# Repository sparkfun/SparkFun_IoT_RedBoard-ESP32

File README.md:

SparkFun IoT RedBoard - ESP32
========================================

[*SparkFun IoT RedBoard - ESP32 (WRL-19177)*](https://www.sparkfun.com/products/19177)

The [SparkFun IoT RedBoard](www.sparkfun.com/products/19177) is an ESP32 Development Board that includes everything but the kitchen sink! Espressif's ESP32 WROOM is a powerful WiFi and Bluetooth® MCU module that targets a wide variety of applications. At the core of this module is the ESP32-D0WDQ6 chip which is designed to be both scalable and adaptive. The IoT RedBoard can target a wide variety of applications, ranging from low-power sensor networks to the most demanding tasks, such as voice encoding, music streaming, and MP3 decoding. The IoT ReadBoard also utilizes our handy Qwiic Connect System which means no soldering or shields are required to connect it to the rest of your system!

The USB-to-serial is achieved with a USB-C connector with through hole anchoring and the ubiquitous CH340G requiring fewer driver installs. We've included 3.3V voltage translation and a [Qwiic connector](https://www.sparkfun.com/qwiic) to the edge of the board to allow for quick and seamless connection to our ever-growing line of I<sup>2</sup>C based [Qwiic products](https://www.sparkfun.com/qwiic#products). The board even includes a microSD socket if your application requires you to log and save data to a memory card.

The operating system is freeRTOS with LwIP; TLS 1.2 with hardware acceleration is built in as well. Secure (encrypted) over the air (OTA) upgrade is also supported, so that users can upgrade their products even after their release, at minimum cost and effort.

Repository Contents
-------------------

* **/Documents** - Data sheets, additional product information
* **/Hardware** - Eagle design files (.brd, .sch)

Documentation
--------------
* **[SparkFun Fritzing Part](https://github.com/sparkfun/Fritzing_Parts/blob/main/products/19177_sfe_iot_redboard_esp32_development_board.fzpz)** - Fritzing diagrams for SparkFun products.
* **[Hookup Guide](https://learn.sparkfun.com/tutorials/iot-redboard-esp32-development-board-hookup-guide)** - Basic hookup guide for the SparkFun IoT RedBoard ESP32.

License Information
-------------------

This product is _**open source**_! 

Please review the LICENSE.md file for license information. 

If you have any questions or concerns on licensing, please contact technical support on our [SparkFun forums](https://forum.sparkfun.com/viewforum.php?f=152).

Distributed as-is; no warranty is given.

- Your friends at SparkFun.

_<COLLABORATION CREDIT>_

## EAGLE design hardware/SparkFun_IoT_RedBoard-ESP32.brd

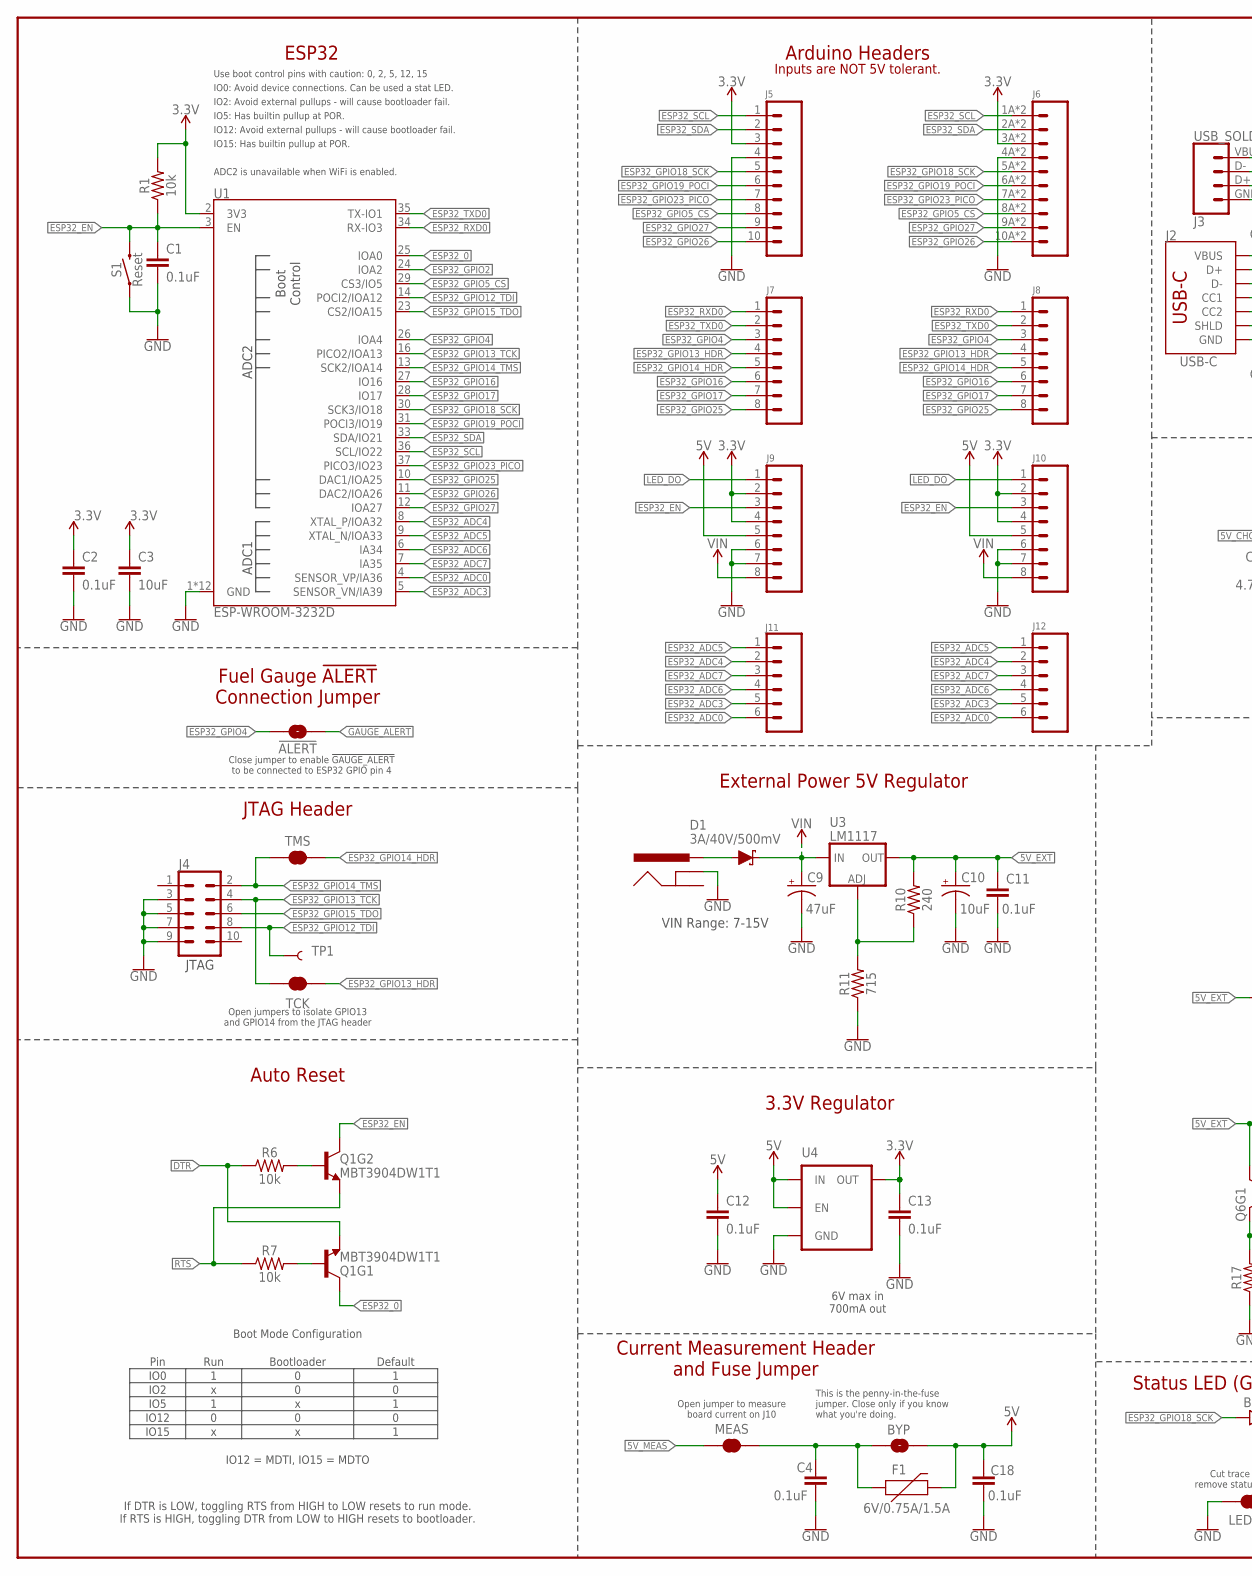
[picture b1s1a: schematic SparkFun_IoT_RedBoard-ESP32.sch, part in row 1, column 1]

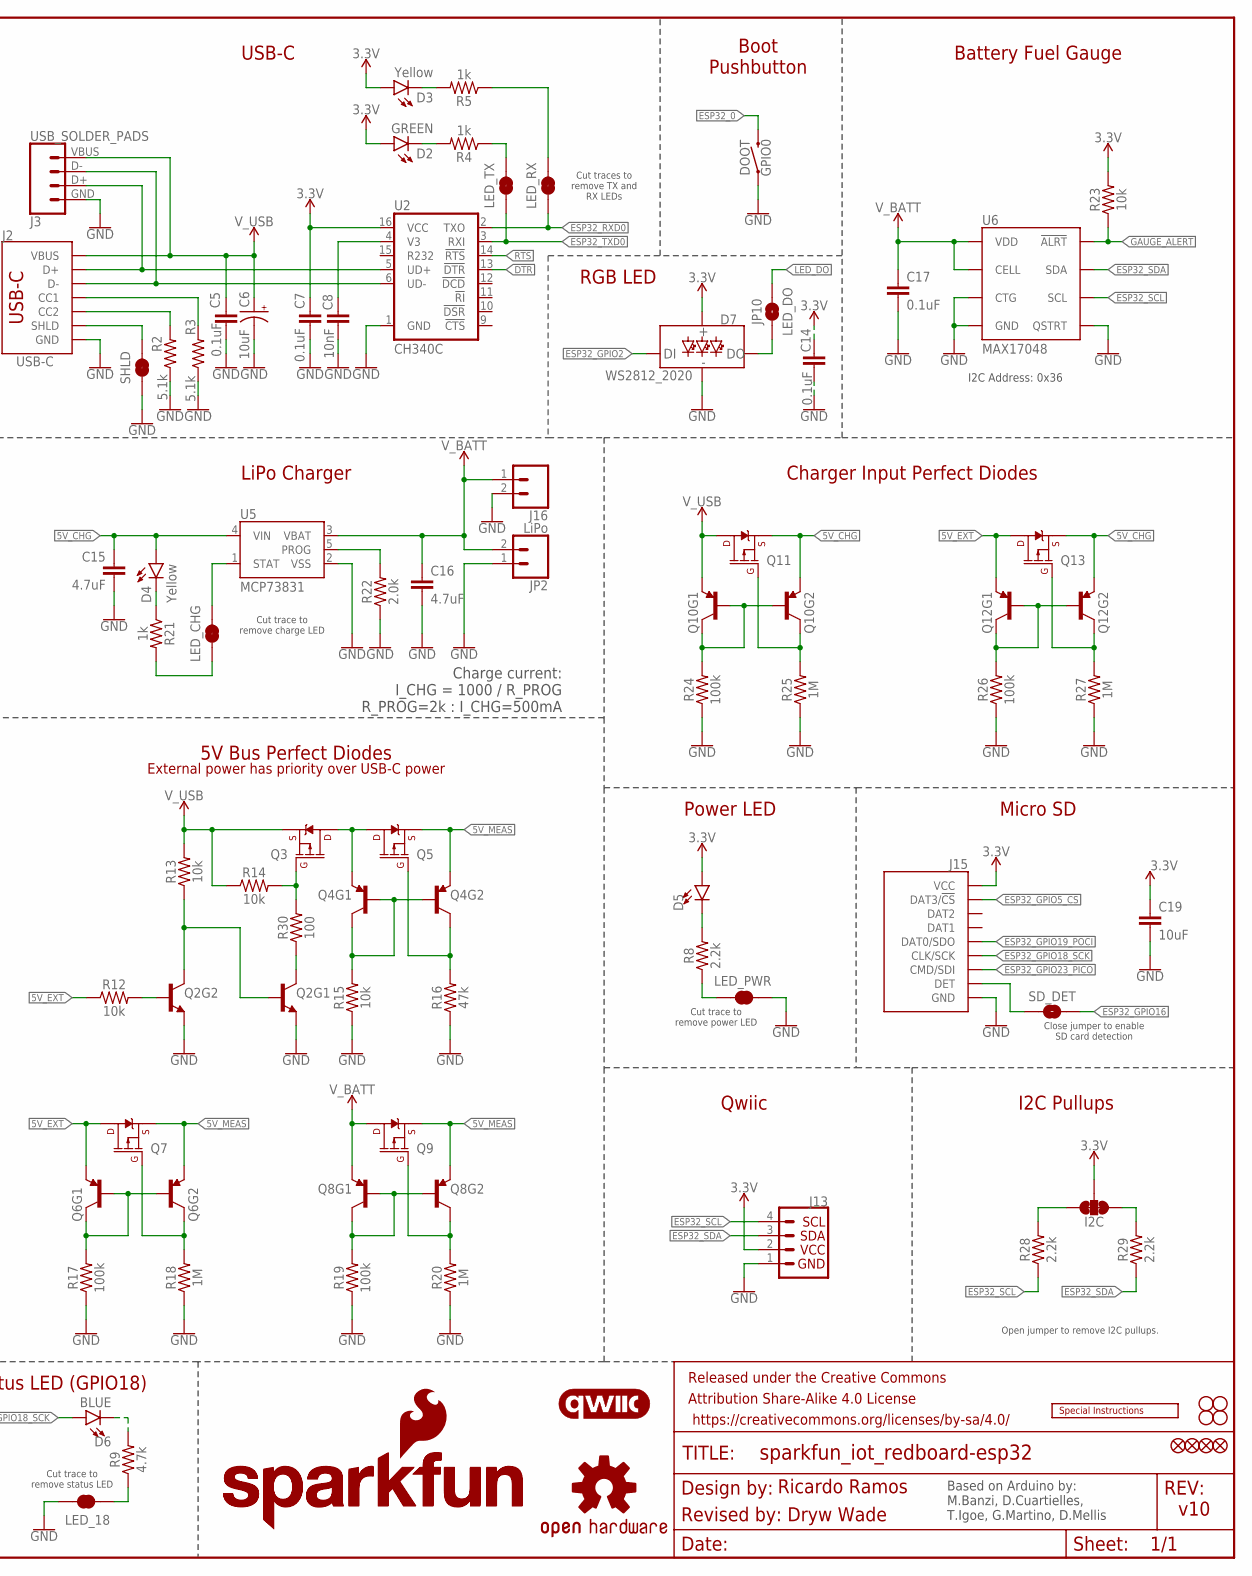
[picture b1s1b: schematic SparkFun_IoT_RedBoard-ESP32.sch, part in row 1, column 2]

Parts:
!ALERT!: JUMPER-SMT_2_NO_SILK; SMT-JUMPER_2_NO_SILK
BYP: JUMPER-SMT_2_NO_SILK; SMT-JUMPER_2_NO_SILK
C1, C2, C4, C5, C7, C11, C12, C13, C14, C17, C18: 0.1uF; 0603
C3, C19: 10uF; 0603
C6, C10: 10uF; EIA3216
C8: 10nF; 0603
C9: 47uF; PANASONIC_D
C15, C16: 4.7uF; 0603
D1: 3A/40V/500mV; SMA-DIODE
D2: GREEN; LED-1206
D3, D4: Yellow; LED-1206
D5: RED; LED-1206
D6: BLUE; LED-1206
D7: WS2812_2020; WS2812-2020
DOOT: GPIO0; TACTILE_SWITCH_SMD_5.2MM
F1: 6V/0.75A/1.5A; 1206
FRAME1: FRAME-LEDGER; CREATIVE_COMMONS
I2C: JUMPER-SMT_3_2-NC_TRACE_SILK; SMT-JUMPER_3_2-NC_TRACE_SILK
J1: 5.5x2.1mm Barrel; POWER_JACK_SMD
J2: USB-C; USB-C-16P-4LAYER-ISOLATED
J3: USB_SOLDER_PADS; USB-SOLDER-PADS
J4: CONN_05X20.05_IN_PTH_SILK; 2X5_PTH_SILK_.05
J5: M10NO_SILK; 1X10_NO_SILK
J6: CONN_10SMD_COMBO-FEMALE; 1X10_SMD_COMBINED
J7, J9: CONN_08NO_SILK_FEMALE_PTH; 1X08_NO_SILK
J8, J10: CONN_08SMD-COMBO-FEMALE; 1X08_SMD_COMBINED
J11: CONN_06NO_SILK_FEMALE_PTH; 1X06_NO_SILK
J12: CONN_06SMD-STRAIGHT-COMBO-FEMALE; 1X06_SMD_STRAIGHT_COMBO
J13: QWIIC_RIGHT_ANGLE; JST04_1MM_RA
J15: MICRO-SD-PUSH-PUSH-EXT-PIN; MICROSD-EXTERNALPIN
J16: CONN_021X02_NO_SILK; 1X02_NO_SILK
JP1, JP7, JP8, JP9: FIDUCIAL1X2; FIDUCIAL-1X2
JP2: LiPo; JST-2-SMD
JP3, JP4, JP5, JP6: STAND-OFF
JP10: LED_DO; SMT-JUMPER_2_NO_SILK
LED_18: JUMPER-SMT_2_NC_TRACE_SILK; SMT-JUMPER_2_NC_TRACE_SILK
LED_CHG: JUMPER-SMT_2_NC_TRACE_SILK; SMT-JUMPER_2_NC_TRACE_SILK
LED_PWR: JUMPER-SMT_2_NC_TRACE_SILK; SMT-JUMPER_2_NC_TRACE_SILK
LED_RX: JUMPER-SMT_2_NC_TRACE_SILK; SMT-JUMPER_2_NC_TRACE_SILK
LED_TX: JUMPER-SMT_2_NC_TRACE_SILK; SMT-JUMPER_2_NC_TRACE_SILK
LOGO1: SFE_LOGO_NAME.1_INCH; SFE_LOGO_NAME_.1
LOGO2: QWIIC_LOGO_5MM; QWIIC_5MM
LOGO3: OSHW-LOGOMINI; OSHW-LOGO-MINI
LOGO5: SPECIAL_INSTRUCTIONS-ORDERING; ORDERING_INSTRUCTIONS
LOGO6: SFE_LOGO_NAME_FLAME.2_INCH; SFE_LOGO_NAME_FLAME_.2
MEAS: JUMPER-COMBO_2_NC_TRACE; COMBO-JUMPER_2_NC_TRACE
Q1: MBT3904DW1T1; SC70-6
Q2: TRANS_NPN_DUAL-MBT3904DW1T1; SC70-6
Q3, Q5, Q7, Q9, Q11, Q13: 20V/4.2A/52mΩ/1.4W; SOT23-3
Q4, Q6, Q8, Q10, Q12: TRANS_PNP_DUALSOT-363; SOT363_PHILIPS
R1, R6, R7, R12, R13, R14, R15, R23: 10k; 0603
R2, R3: 5.1k; 0603
R4, R5, R21: 1k; 0603
R8, R28, R29: 2.2k; 0603
R9: 4.7k; 0603
R10: 240; 0603
R11: 715; 0603
R16: 47k; 0603
R17, R19, R24, R26: 100k; 0603
R18, R20, R25, R27: 1M; 0603
R22: 2.0k; 0603
R30: 100; 0603
S1: Reset; TACTILE_SWITCH_SMD_5.2MM
SD_DET: SD_DET; SMT-JUMPER_2_NO_SILK
SHLD: SHLD; SMT-JUMPER_2_NC_TRACE_SILK
TCK: JUMPER-SMT_2_NC_TRACE_SILK; SMT-JUMPER_2_NC_TRACE_SILK
TMS: JUMPER-SMT_2_NC_TRACE_SILK; SMT-JUMPER_2_NC_TRACE_SILK
TP1: TEST-POINT3; PAD.03X.03
U1: ESP-WROOM-3232D; ESP-WROOM-32D
U2: CH340C; SO016
U3: LM1117; SOT223
U4: XC6222B331MR-G; SOT23-5
U5: MCP73831; SOT23-5
U6: MAX17048; DFN-8

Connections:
3.3V: C2.1, C3.1, C7.1, C13.1, C14.1, C19.1, D2.A, D3.A, D5.A, D7.VCC, I2C.2, J5.3, J6.3A (3), J6.3B (3), J9.2, J9.4, J10.2, J10.4, J13.2, J15.4 (VCC), R1.2, R23.2, U1.2 (3V3), U2.16 (VCC), U4.5 (OUT)
5V: BYP.2, C12.1, C18.1, F1.2, J9.5, J10.5, U4.1 (IN), U4.3 (EN)
5V_CHG: C15.1, D4.A, Q10.4 (E), Q11.2 (S), Q12.4 (E), Q13.2 (S), U5.4 (VIN)
5V_EXT: C10.+, C11.1, Q6.1 (E), Q7.3 (D), Q12.1 (E), Q13.3 (D), R10.2, R12.1, U3.2 (OUT), U3.4 (OUT)
5V_MEAS: MEAS.1, MEAS.3 (1), Q4.4 (E), Q5.2 (S), Q6.4 (E), Q7.2 (S), Q8.4 (E), Q9.2 (S)
!DTR!: Q1.4 (E), R6.1, U2.13 (!DTR)
!GAUGE_ALERT!: !ALERT!.1, R23.1, U6.5 (!ALRT)
!RTS!: Q1.1 (E), R7.1, U2.14 (!RTS)
CC1: J2.A5 (CC1), R3.2
CC2: J2.B5 (CC2), R2.2
D+: J2.A6 (D+), J2.B6 (D+), J3.D+ (3), U2.5 (UD+)
D-: J2.A7 (D-), J2.B7 (D-), J3.D- (2), U2.6 (UD-)
ESP32_0: DOOT.3 (2), DOOT.4 (2), Q1.3 (C), U1.25 (IOA0)
ESP32_ADC0: J11.6, J12.6, U1.4 (SENSOR_VP/IA36)
ESP32_ADC3: J11.5, J12.5, U1.5 (SENSOR_VN/IA39)
ESP32_ADC4: J11.2, J12.2, U1.8 (XTAL_P/IOA32)
ESP32_ADC5: J11.1, J12.1, U1.9 (XTAL_N/IOA33)
ESP32_ADC6: J11.4, J12.4, U1.6 (IA34)
ESP32_ADC7: J11.3, J12.3, U1.7 (IA35)
ESP32_EN: C1.1, J9.3, J10.3, Q1.6 (C), R1.1, S1.3 (2), S1.4 (2), U1.3 (EN)
ESP32_GPIO2: D7.DI, U1.24 (IOA2)
ESP32_GPIO4: !ALERT!.2, J7.3, J8.3, U1.26 (IOA4)
ESP32_GPIO5_!CS!: J5.8, J6.8A (8), J6.8B (8), J15.2 (DAT3/!CS!), U1.29 (CS3/IO5)
ESP32_GPIO12_TDI: J4.8, TP1.1, U1.14 (POCI2/IOA12)
ESP32_GPIO13_HDR: J7.4, J8.4, TCK.2
ESP32_GPIO13_TCK: J4.4, TCK.1, U1.16 (PICO2/IOA13)
ESP32_GPIO14_HDR: J7.5, J8.5, TMS.2
ESP32_GPIO14_TMS: J4.2, TMS.1, U1.13 (SCK2/IOA14)
ESP32_GPIO15_TDO: J4.6, U1.23 (CS2/IOA15)
ESP32_GPIO16: J7.6, J8.6, SD_DET.2, U1.27 (IO16)
ESP32_GPIO17: J7.7, J8.7, U1.28 (IO17)
ESP32_GPIO18_SCK: D6.A, J5.5, J6.5A (5), J6.5B (5), J15.5 (CLK/SCK), U1.30 (SCK3/IO18)
ESP32_GPIO19_POCI: J5.6, J6.6A (6), J6.6B (6), J15.7 (DAT0/SDO), U1.31 (POCI3/IO19)
ESP32_GPIO23_PICO: J5.7, J6.7A (7), J6.7B (7), J15.3 (CMD/SDI), U1.37 (PICO3/IO23)
ESP32_GPIO25: J7.8, J8.8, U1.10 (DAC1/IOA25)
ESP32_GPIO26: J5.10, J6.10A (10), J6.10B (10), U1.11 (DAC2/IOA26)
ESP32_GPIO27: J5.9, J6.9A (9), J6.9B (9), U1.12 (IOA27)
ESP32_RXD0: J7.1, J8.1, LED_RX.1, U1.34 (RX-IO3), U2.2 (TXO)
ESP32_SCL: J5.1, J6.1A (1), J6.1B (1), J13.4, R28.1, U1.36 (SCL/IO22), U6.7 (SCL)
ESP32_SDA: J5.2, J6.2A (2), J6.2B (2), J13.3, R29.1, U1.33 (SDA/IO21), U6.8 (SDA)
ESP32_TXD0: J7.2, J8.2, LED_TX.1, U1.35 (TX-IO1), U2.3 (RXI)
GND: C1.2, C2.2, C3.2, C4.2, C5.2, C6.-, C7.2, C8.2, C9.-, C10.-, C11.2, C12.2, C13.2, C14.2, C15.2, C16.2, C17.2, C18.2, C19.2, D7.GND, DOOT.1, DOOT.2 (1), J1.GND (GNDBREAK), J2.GND, J2.GND2 (GND), J3.GND (4), J4.3, J4.5, J4.7, J4.9, J5.4, J6.4A (4), J6.4B (4), J9.6, J9.7, J10.6, J10.7, J13.1, J15.6 (GND), J15.10 (GND), J15.11 (GND), J15.12 (GND), J15.13 (GND), J16.2, JP2.1 (2), LED_18.1, LED_PWR.1, Q2.1 (E), Q2.4 (E), R2.1, R3.1, R11.1, R15.1, R16.1, R17.1, R18.1, R19.1, R20.1, R22.1, R24.1, R25.1, R26.1, R27.1, S1.1, S1.2 (1), SHLD.1, U1.1 (GND), U1.15 (GND), U1.38 (GND), U1.GND, U1.GNDT1 (GND), U1.GNDT2 (GND), U1.GNDT3 (GND), U1.GNDT4 (GND), U1.GNDT5 (GND), U1.GNDT6 (GND), U1.GNDT7 (GND), U1.GNDT8 (GND), U2.1 (GND), U4.2 (GND), U5.2 (VSS), U6.1 (CTG), U6.4 (GND), U6.6 (QSTRT), U6.9 (GND)
LED_DO: J9.1, J10.1, JP10.2
unnamed: LED_CHG.2, U5.1 (STAT)
unnamed: D5.C, R8.2
unnamed: D6.C, R9.2
unnamed: LED_CHG.1, R21.2
unnamed: D2.C, R4.2
unnamed: C8.1, U2.4 (V3)
unnamed: D3.C, R5.2
unnamed: Q6.2 (B), Q6.5 (B), Q6.6 (C), R17.2
unnamed: Q3.1 (G), R14.2, R30.2
unnamed: Q6.3 (C), Q7.1 (G), R18.2
unnamed: Q2.3 (C), R30.1
unnamed: Q4.2 (B), Q4.5 (B), Q4.6 (C), R15.2
unnamed: Q8.2 (B), Q8.5 (B), Q8.6 (C), R19.2
unnamed: R22.2, U5.5 (PROG)
unnamed: R10.1, R11.2, U3.1 (ADJ)
unnamed: Q4.3 (C), Q5.1 (G), R16.2
unnamed: Q8.3 (C), Q9.1 (G), R20.2
unnamed: I2C.3, R28.2
unnamed: BYP.1, C4.1, F1.1, MEAS.2, MEAS.4 (2)
unnamed: I2C.1, R29.2
unnamed: Q2.2 (B), R12.2
unnamed: Q2.5 (B), Q2.6 (C), R13.1
unnamed: Q10.3 (C), Q11.1 (G), R25.2
unnamed: Q1.5 (B), R7.2
unnamed: Q1.2 (B), R6.2
unnamed: Q10.2 (B), Q10.5 (B), Q10.6 (C), R24.2
unnamed: J15.9 (DET), SD_DET.1
unnamed: Q12.3 (C), Q13.1 (G), R27.2
unnamed: Q12.2 (B), Q12.5 (B), Q12.6 (C), R26.2
unnamed: LED_TX.2, R4.1
unnamed: LED_RX.2, R5.1
unnamed: D4.C, R21.1
unnamed: LED_PWR.2, R8.1
unnamed: LED_18.2, R9.1
unnamed: D7.DO, JP10.1
PWRIN: D1.A, J1.VIN0 (PWR)
SHLD: J2.SHLD1 (SHLD), J2.SHLD2 (SHLD), J2.SHLD3 (SHLD), J2.SHLD4 (SHLD), J2.SHLD5 (SHLD), J2.SHLD6 (SHLD), J2.SHLD7 (SHLD), J2.SHLD8 (SHLD), SHLD.2
VIN: C9.+, D1.C, J9.8, J10.8, U3.3 (IN)
VUSB_PROT: Q3.3 (D), Q4.1 (E), Q5.3 (D)
V_BATT: C16.1, C17.1, J16.1, JP2.2 (1), Q8.1 (E), Q9.3 (D), U5.3 (VBAT), U6.2 (CELL), U6.3 (VDD)
V_USB: C5.1, C6.+, J2.VBUS1 (VBUS), J2.VBUS2 (VBUS), J3.VBUS (1), Q3.2 (S), Q10.1 (E), Q11.3 (D), R13.2, R14.1

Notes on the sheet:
Based on Arduino by: M.Banzi, D.Cuartielles, T.Igoe, G.Martino, D.Mellis
Ricardo Ramos
v10
This is the penny-in-the-fuse jumper. Close only if you know what you're doing.
JTAG
J12
J11
J10
If DTR is LOW, toggling RTS from HIGH to LOW resets to run mode. If RTS is HIGH, toggling DTR from LOW to HIGH resets to bootloader.
VIN Range: 7-15V
6V max in 700mA out
Charge current: I_CHG = 1000 / R_PROG R_PROG=2k : I_CHG=500mA
ESP32
Arduino Headers
USB-C
Battery Fuel Gauge
LiPo Charger
Charger Input Perfect Diodes
5V Bus Perfect Diodes
Power LED
Micro SD
Qwiic
I2C Pullups
External Power 5V Regulator
3.3V Regulator
JTAG Header
Fuel Gauge !ALERT! Connection Jumper
Auto Reset
Current Measurement Header and Fuse Jumper
Boot Pushbutton
Status LED (GPIO18)
External power has priority over USB-C power
Inputs are NOT 5V tolerant.
I2C Address: 0x36
Open jumpers to isolate GPIO13 and GPIO14 from the JTAG header
Close jumper to enable !GAUGE_ALERT! to be connected to ESP32 GPIO pin 4
Open jumper to measure board current on J10
Open jumper to remove I2C pullups.
Revised by: Dryw Wade
RGB LED

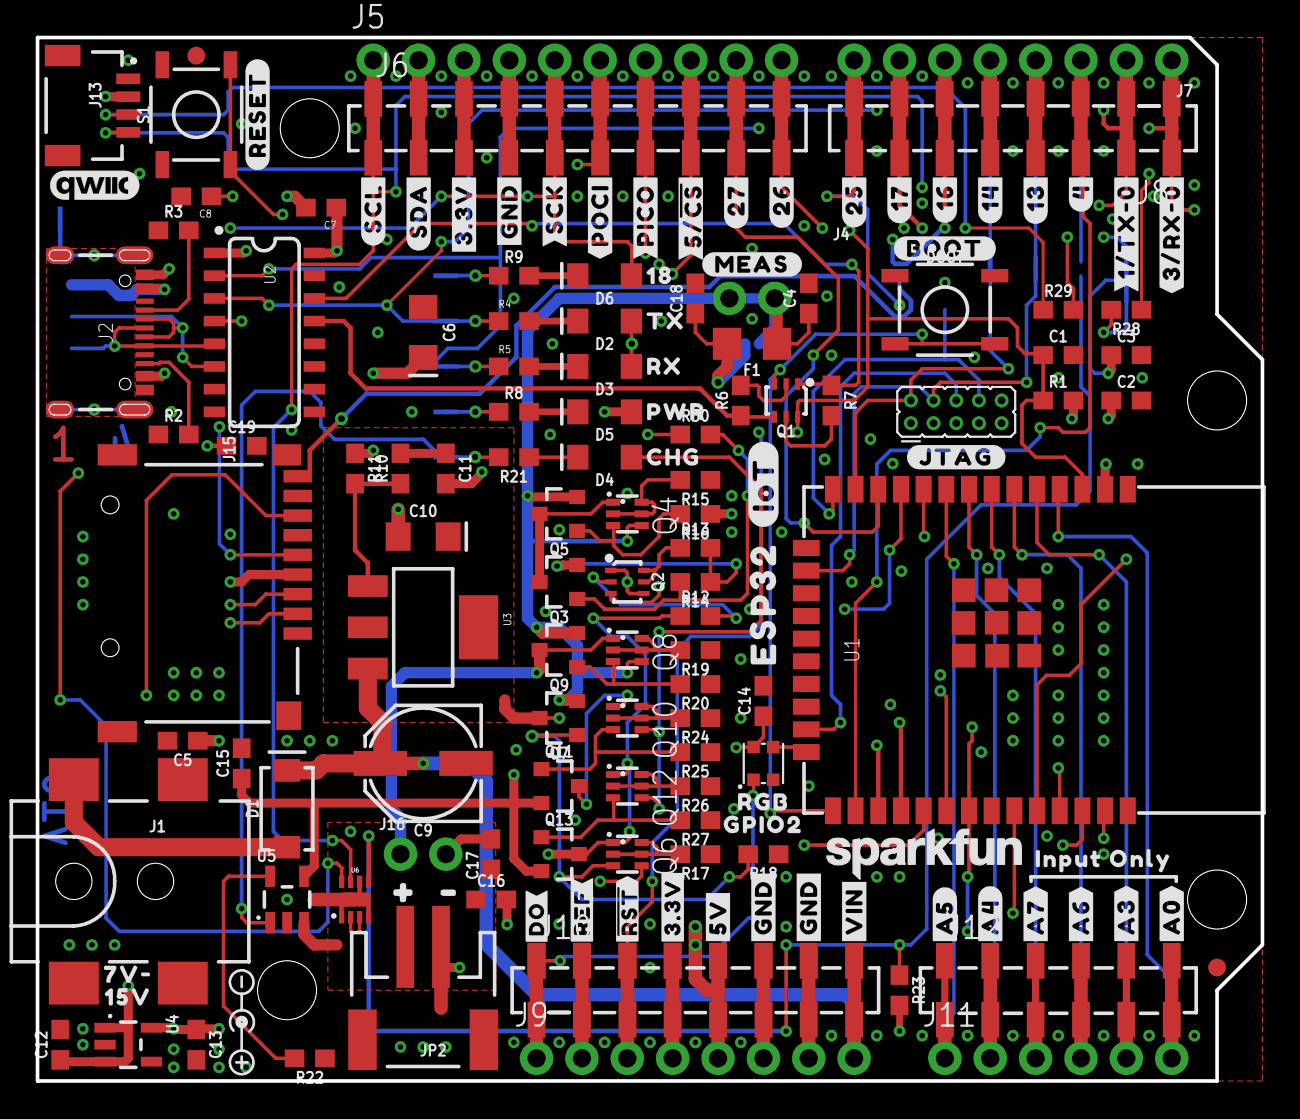
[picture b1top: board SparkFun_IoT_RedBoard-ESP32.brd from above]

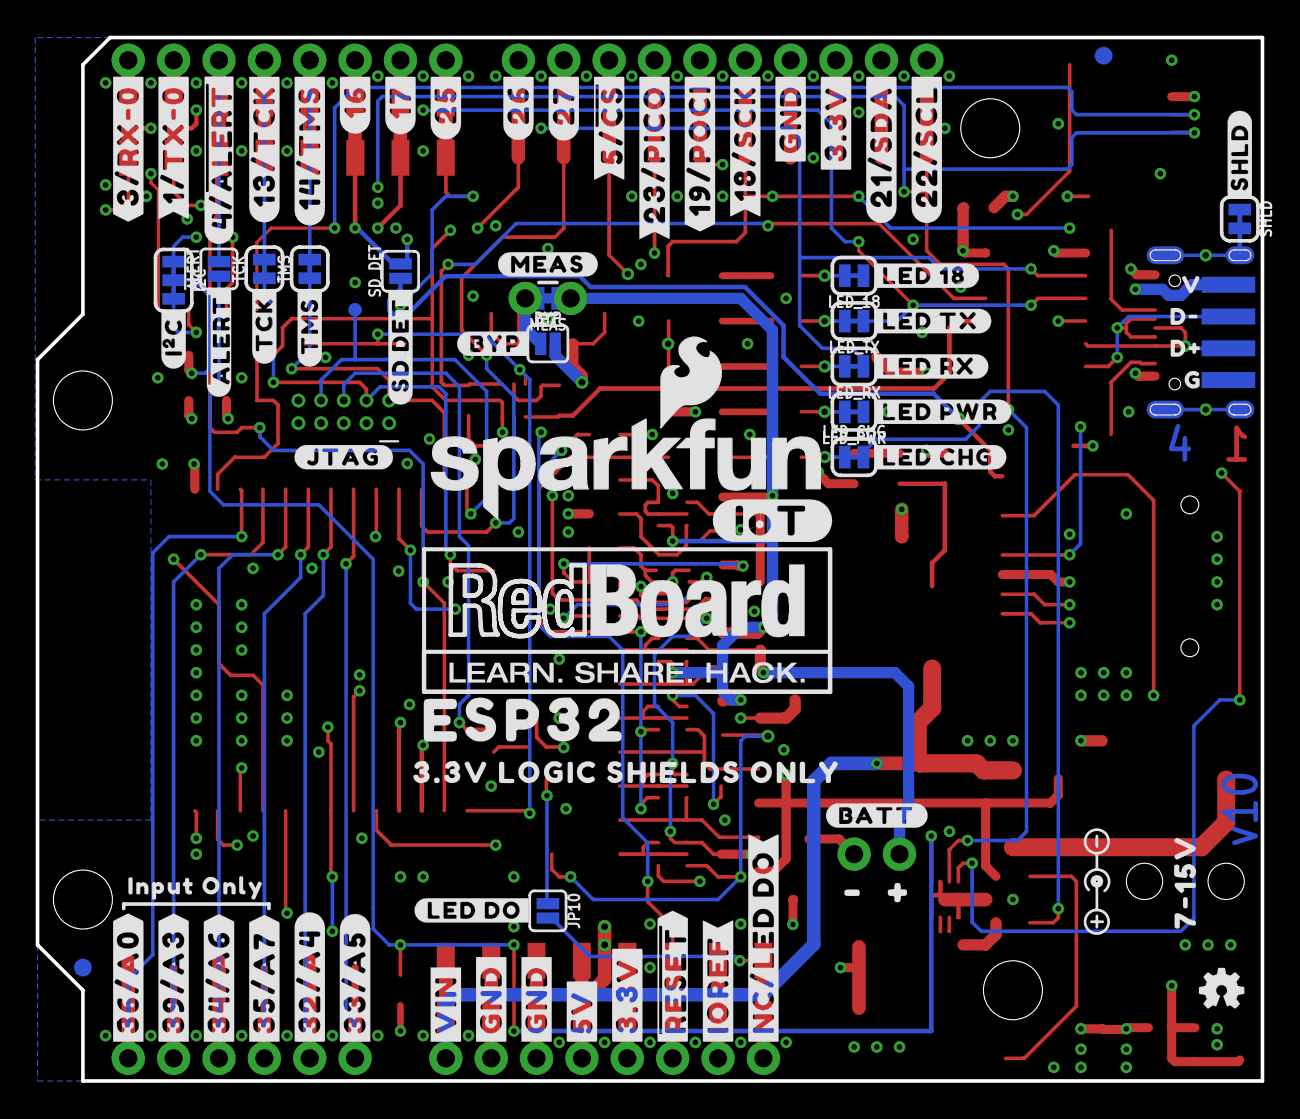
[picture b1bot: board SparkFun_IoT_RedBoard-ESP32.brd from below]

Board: 4 copper layers, 68.6 x 58.4 mm, 235 parts (81 on the bottom side), 84 nets.

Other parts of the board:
U$3: #SCL#34
U$4: #SDA#33
U$5: #3#3V#33
U$6: #GND#32
U$7: #SCK#31
U$8: #POCI#30
U$9: #PICO#29
U$10: 1836
U$11, U$42: #MEAS#1851
U$12: #27#27
U$13: #26#26
U$14: TX1838
U$15: RX1839
U$16: PWR1837
U$17: CHG1840
U$18: #25#18
U$19: #17#17
U$20: #16#15
U$21: #14#14
U$22: #13#5
U$23: #4#2
U$24: #3#RX#0#4
U$25: #3#RX#0#0
U$26: #RESET#1842
U$27: #BOOT#1841
U$28, U$46: #JTAG#1847
U$29: #A0#1843
U$30: #A3#1843
U$31: #A6#1843
U$32: #A7#1843
U$33: #A4#1843
U$34: #A5#1843
U$35: #VIN#1843
U$36, U$37: #GND#1844
U$38: #5V#1845
U$39: #3#3V#1845
U$40: ##RST##1845
U$41: #REF#1846
U$43, U$86: #1849
U$44, U$88: #1850
U$45: #BATT#1848
U$47: #IOT#132321874
U$48: ESP321855
U$49: #LED_18#0
U$50: #39#A3#321862
U$51: #36#A0#321862
U$52: #33#A5#0
U$53: #35#A7#321862
U$54: #32#A4#32321865
U$55: #34#A6#321862
U$56: #VIN#321862
U$57, U$60: #GND#321863
U$58: #5V#321864
U$59: #3#3V#321864
U$61: ##RESET##321864
U$62: #IOREF#321865
U$63: #5##CS##0
U$64: #BYP#0
U$65: RGB0
U$66: #13#TCK#32321869
U$67: #14#TMS#32321869
U$68: #16#32321869
U$69: #17#32321869
U$70: #25#32321869
U$71: #26#32321869
U$72: #5##CS##32321869
U$73: #23#PICO#321866
U$74: #19#POCI#321866
U$75: #18#SCK#32321869
U$76: #21#SDA#32321869
U$77: #22#SCL#32321869
U$78: #27#32321869
U$79: #GND#321866
U$80: #3#3V#321866
U$81: #SHLD#0
U$82: #I�C#0
U$83: D#32321863
U$84: D#32321862
U$85: G32321864
U$87: V323252
U$89: #DO#0
U$90: ##ALERT##1852
U$91: #TMS#1854
U$92: #TCK#1853
U$93: ESP32321856
U$94, U$99: POLARITY_MARKING_CENTER_POSITIVE#JPG
U$96, U$97: INPUT_ONLY321867
U$98: REDBOARD_LOGO
U$100: #IOT#132321869
U$101: 7#15V32321861
U$102: #4##ALERT##0
U$103: 3#3V_LOGIC_SHIELDS_ONLY132321876
U$104: #1#TX#0#0
U$105: #1#TX#0#2
U$106: 7V#0
U$107: 15V0
U$108: #SD_DET#0
U$109: #LED_TX#0
U$110: #LED_RX#0
U$111: #LED_PWR#0
U$112: #LED_CHG#0
U$113: GPIO20
U$114: #LED_DO#1
U$115: #NC#LED_DO#0

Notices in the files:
parts and their libraries:
SparkFun-Aesthetics: Licensing: CC v3.0 Share-Alike You are welcome to use this library for commercial purposes.
SparkFun-DiscreteSemi: Licensing: Creative Commons ShareAlike 4.0 International - https://creativecommons.org/licenses/by-sa/4.0
SparkFun-Aesthetics: Released under the Creative Commons
